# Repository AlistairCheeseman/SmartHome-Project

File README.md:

SmartHome-Project
=================

Final Year degree project to create a set of devices to create a smart home.

Hardware files are created in eagle with PDFs of finished pcbs labelled with which pcb layer they are. Hardware files are created from scratch and a custom library has been created for components not in the default eagle library.

Software has three sections.

	-	www
		copy this to the production web server. the files are based on php 5.6 HTML 5, using ajax and highcharts charting components (http://www.highcharts.com/ - free for non commercial uses).
		
	-	LFS
		This contains a set of manually written build scripts (toolchain and Filesystem) and pre-writted configuration files. After both files (install-*.sh) have been executed on a linux machine there will be a working Linux filesystem. Be sure to change configuration file (buildscript.sh) variables to suit your setup!

	-	Apps
		This contains source for all custom written applications on the server.

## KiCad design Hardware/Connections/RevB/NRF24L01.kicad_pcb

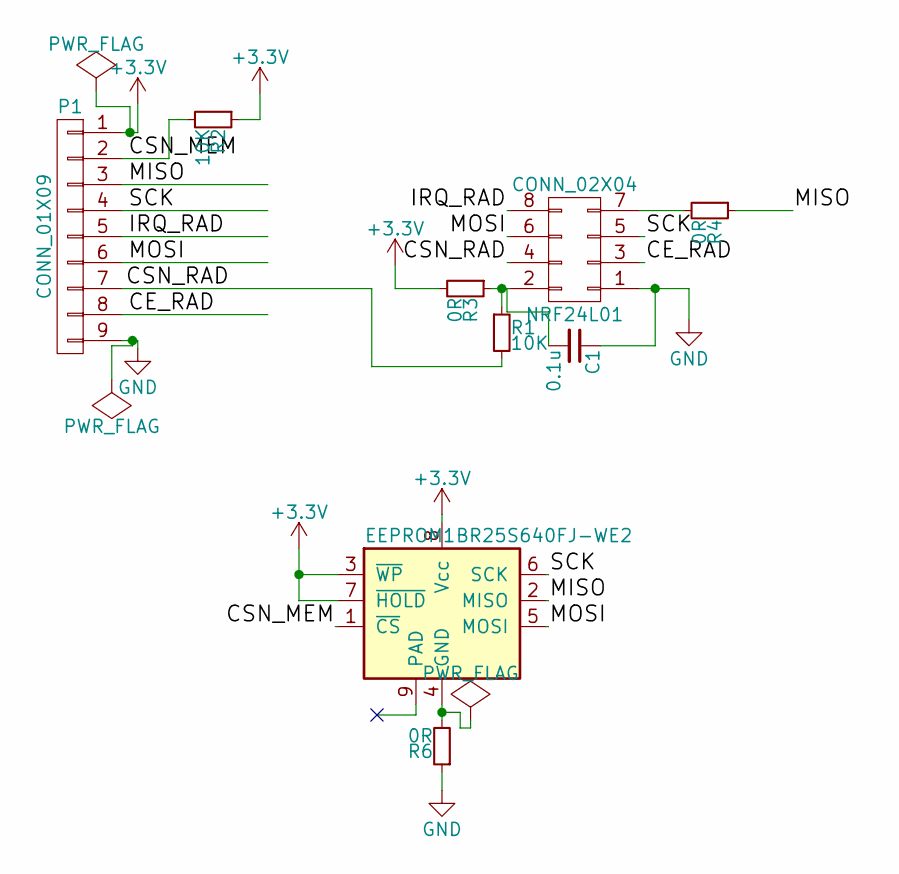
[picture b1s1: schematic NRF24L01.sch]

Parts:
C1: 0.1u; C_1206_HandSoldering
EEPROM1: BR25S640FJ-WE2; SOP8
NRF24L01: CONN_02X04; Pin_Header_Straight_2x04SMD
P1: CONN_01X09; Pin_Header_Straight_1x09
R1, R2: 10K; R_1206_HandSoldering
R3, R4, R6: 0R; R_1206_HandSoldering

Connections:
+3V3: EEPROM1.3 (~WP), EEPROM1.7 (~HOLD), EEPROM1.8 (Vcc), P1.1, R2.1, R3.2
/CE_RAD: NRF24L01.3, P1.8
/CSN_MEM: EEPROM1.1 (~CS), P1.2, R2.2
/CSN_RAD: NRF24L01.4, P1.7, R1.2
/IRQ_RAD: NRF24L01.8, P1.5
/MISO: EEPROM1.2 (MISO), P1.3, R4.1
/MOSI: EEPROM1.5 (MOSI), NRF24L01.6, P1.6
/SCK: EEPROM1.6 (SCK), NRF24L01.5, P1.4
GND: C1.1, NRF24L01.1, P1.9, R6.1
unnamed: C1.2, NRF24L01.2, R1.1, R3.1
unnamed: EEPROM1.4 (GND), R6.2
unnamed: NRF24L01.7, R4.2

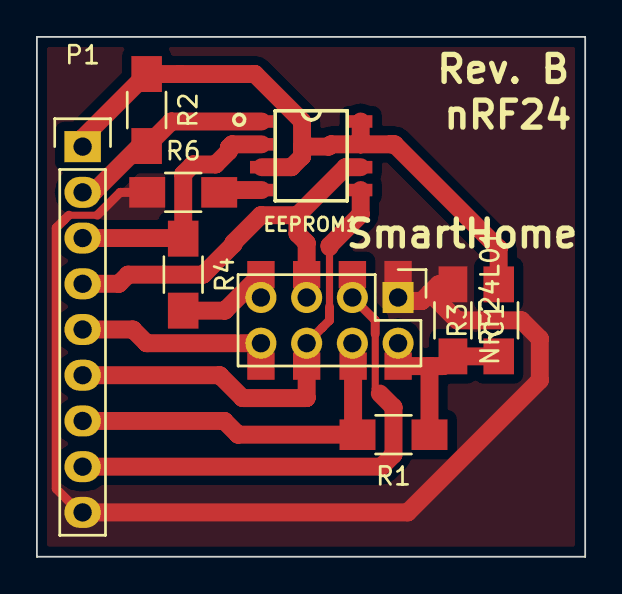
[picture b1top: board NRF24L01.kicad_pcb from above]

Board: 2 copper layers, 30.5 x 28.9 mm, 9 parts (0 on the bottom side), 12 nets.

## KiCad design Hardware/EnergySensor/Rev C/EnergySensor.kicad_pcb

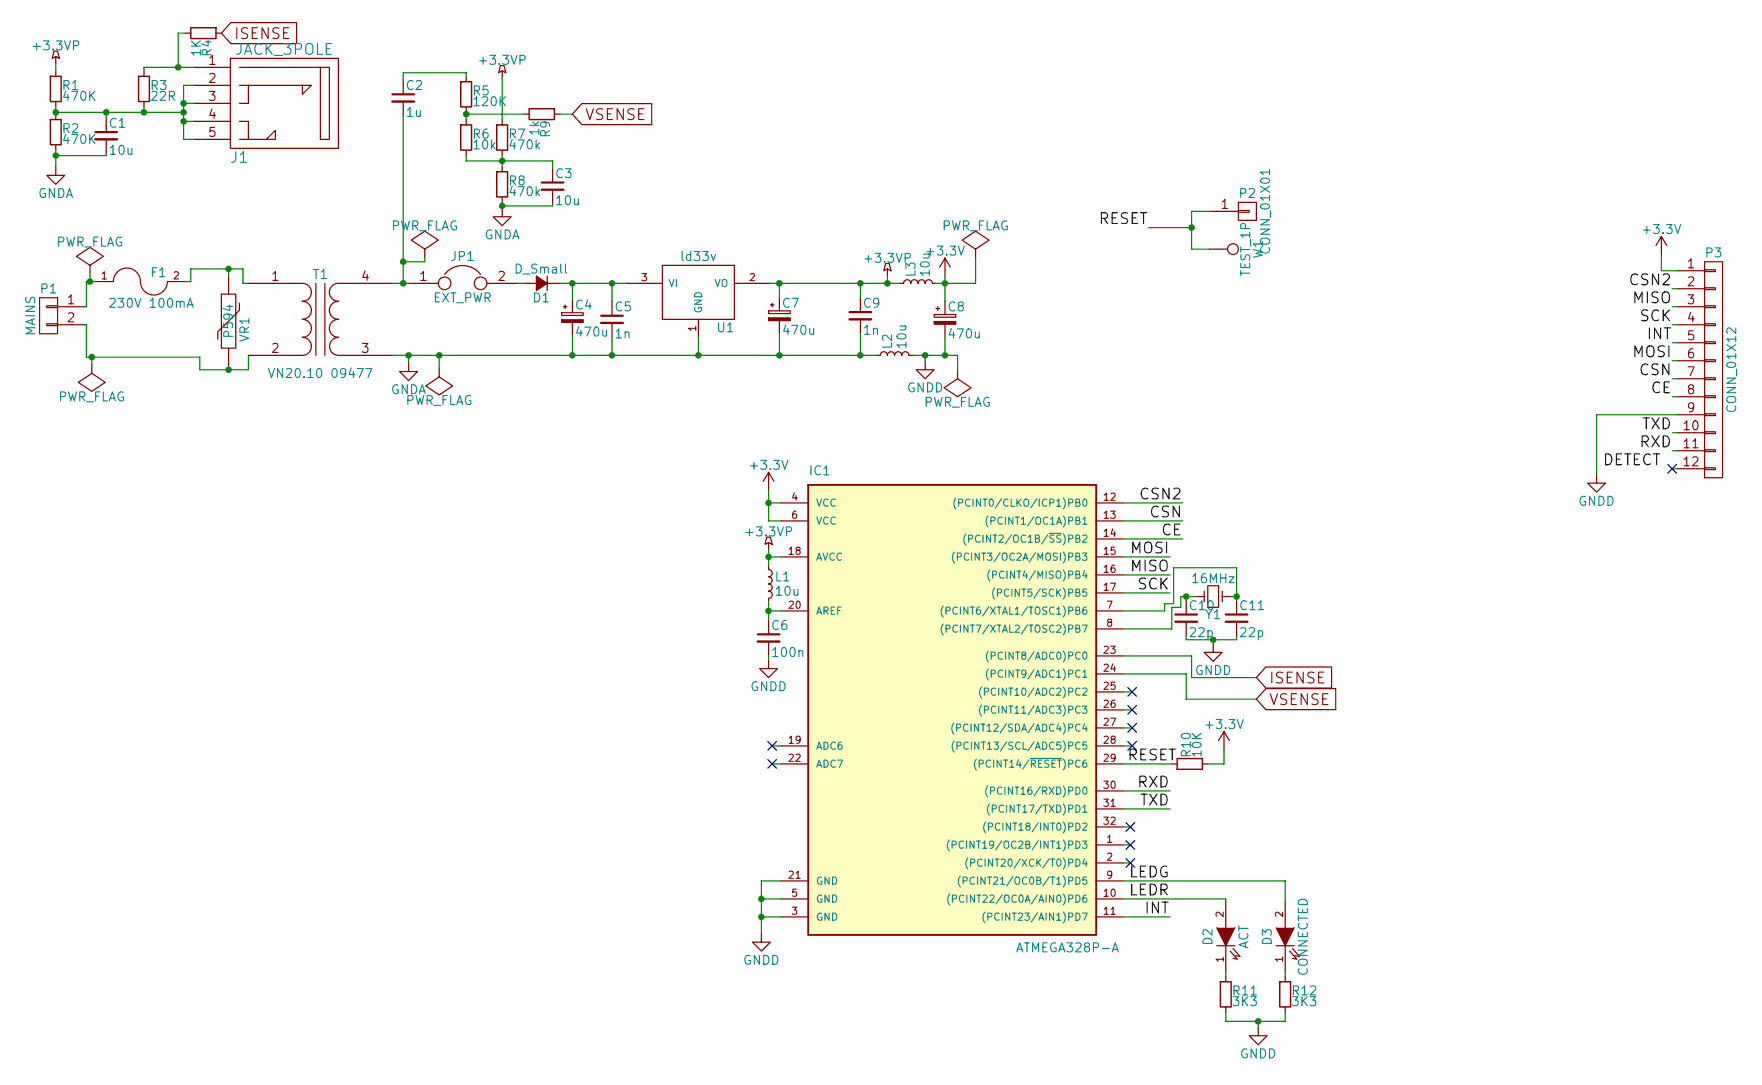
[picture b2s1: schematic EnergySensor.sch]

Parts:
C1, C3: 10u; C_1206_HandSoldering
C2: 1u; C_1206_HandSoldering
C4, C7, C8: 470u; c_elec_5x4.5
C5, C9: 1n; C_1206_HandSoldering
C6: 100n; C_1206_HandSoldering
C10, C11: 22p; C_1206_HandSoldering
D1: D_Small; MELF-RM10_Universal_Handsoldering
D2: ACT; LED-0805
D3: CONNECTED; LED-0805
F1: 230V 100mA; Fuse_SMD1206_HandSoldering
IC1: ATMEGA328P-A; TQFP-32_7x7mm_Pitch0.8mm
J1: JACK_3POLE
JP1: EXT_PWR; Socket_Strip_Straight_1x02
L1, L2, L3: 10u; Inductor_1212
P1: MAINS; AK300-2
P2: CONN_01X01; Pin_Header_Straight_1x01
P3: CONN_01X12; Socket_Strip_Angled_1x12
R1, R2: 470K; R_1206_HandSoldering
R3: 22R; R_1206_HandSoldering
R4: 1K; R_1206_HandSoldering
R5: 120K; R_1206_HandSoldering
R6: 10k; R_1206_HandSoldering
R7, R8: 470k; R_1206_HandSoldering
R9: 1k; R_1206_HandSoldering
R10: 10K; R_1206_HandSoldering
R11, R12: 3K3; R_1206_HandSoldering
T1: VN20.10 09477; TEZ-22x24
U1: ld33v; TO-220_Neutral123_Vertical
VR1: P594; RV_Disc_D7_W3.4_P5
W1: TEST_1P; Measurement_Point_Round-SMD-Pad_Big
Y1: 16MHz; Crystal_HC49-SD_SMD

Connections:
+3.3VP: C7.1, C9.1, IC1.18 (AVCC), L1.1, L3.1, R1.1, R7.1, U1.2 (VO)
+3V3: C8.1, IC1.4 (VCC), IC1.6 (VCC), L3.2, P3.1, R10.2
/CE: IC1.14 ((PCINT2/OC1B/~SS~)PB2), P3.8
/CSN: IC1.13 ((PCINT1/OC1A)PB1), P3.7
/CSN2: IC1.12 ((PCINT0/CLKO/ICP1)PB0), P3.2
/INT: IC1.11 ((PCINT23/AIN1)PD7), P3.5
/LEDG: D3.2 (A), IC1.9 ((PCINT21/OC0B/T1)PD5)
/LEDR: D2.2 (A), IC1.10 ((PCINT22/OC0A/AIN0)PD6)
/MISO: IC1.16 ((PCINT4/MISO)PB4), P3.3
/MOSI: IC1.15 ((PCINT3/OC2A/MOSI)PB3), P3.6
/RESET: IC1.29 ((PCINT14/~RESET~)PC6), P2.1, R10.1, W1.1
/RXD: IC1.30 ((PCINT16/RXD)PD0), P3.11
/SCK: IC1.17 ((PCINT5/SCK)PB5), P3.4
/TXD: IC1.31 ((PCINT17/TXD)PD1), P3.10
GNDA: C1.2, C3.2, C4.2, C5.2, C7.2, C9.2, L2.1, R2.2, R8.2, T1.3 (SA), U1.1 (GND)
GNDD: C6.2, C8.2, C10.2, C11.2, IC1.3 (GND), IC1.5 (GND), IC1.21 (GND), L2.2, P3.9, R11.2, R12.2
ISENSE: IC1.23 ((PCINT8/ADC0)PC0), R4.1
unnamed: C1.1, J1.2, J1.3, J1.4, J1.5, R1.2, R2.1, R3.2
unnamed: C2.1, R5.1
unnamed: C2.2, JP1.1, T1.4 (SB)
unnamed: C3.1, R6.2, R7.2, R8.1
unnamed: C4.1, C5.1, D1.1 (K), U1.3 (VI)
unnamed: C6.1, IC1.20 (AREF), L1.2
unnamed: C10.1, IC1.8 ((PCINT7/XTAL2/TOSC2)PB7), Y1.2
unnamed: C11.1, IC1.7 ((PCINT6/XTAL1/TOSC1)PB6), Y1.1
unnamed: D1.2 (A), JP1.2
unnamed: D2.1 (K), R11.1
unnamed: D3.1 (K), R12.1
unnamed: F1.1, P1.1
unnamed: F1.2, T1.1 (AA), VR1.1
unnamed: J1.1, R3.1, R4.2
unnamed: P1.2, T1.2 (AB), VR1.2
unnamed: R5.2, R6.1, R9.2
VSENSE: IC1.24 ((PCINT9/ADC1)PC1), R9.1

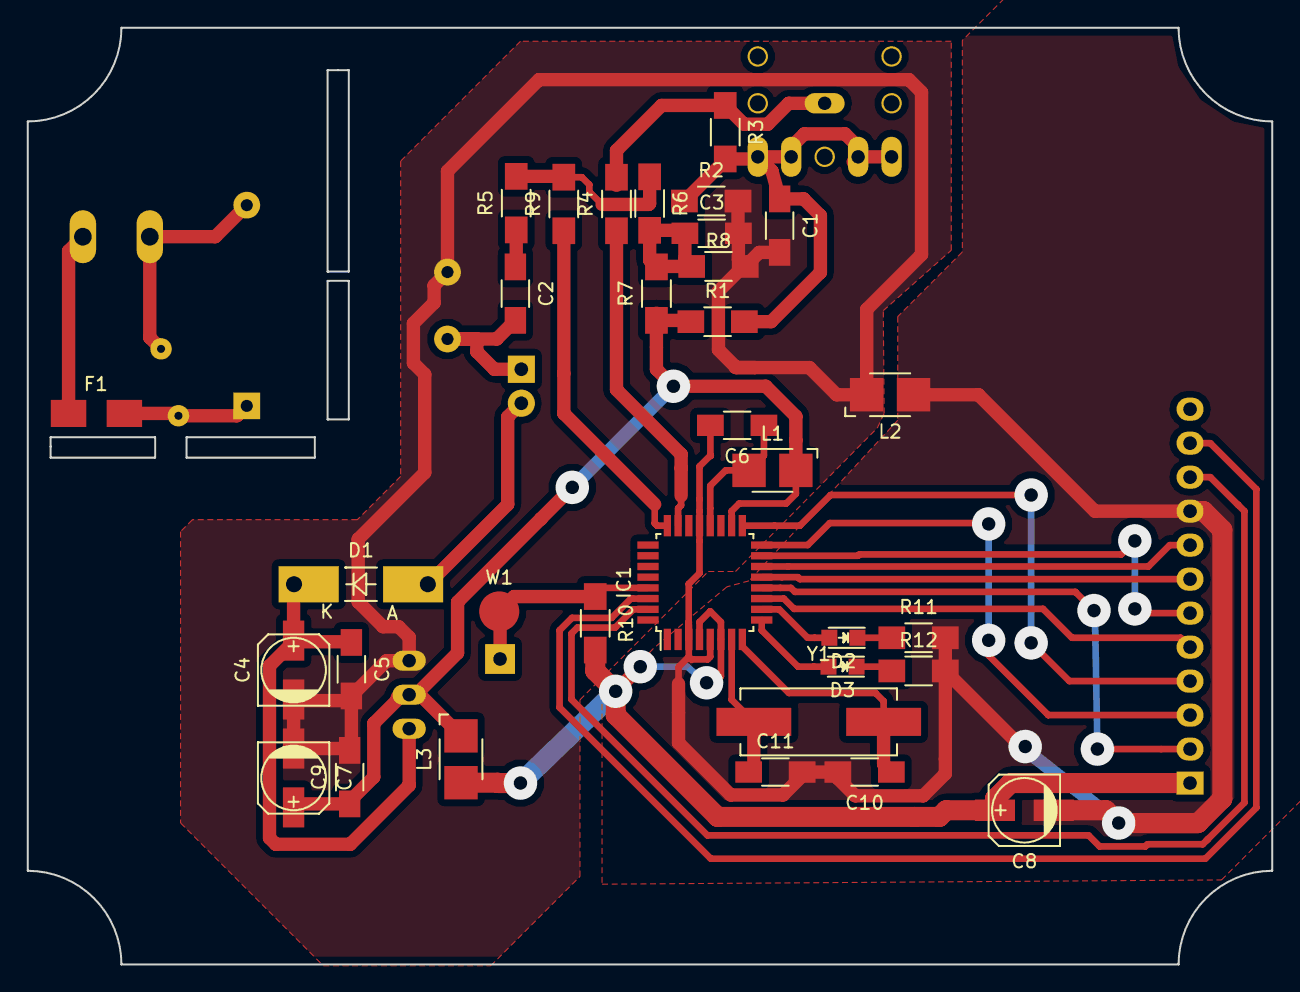
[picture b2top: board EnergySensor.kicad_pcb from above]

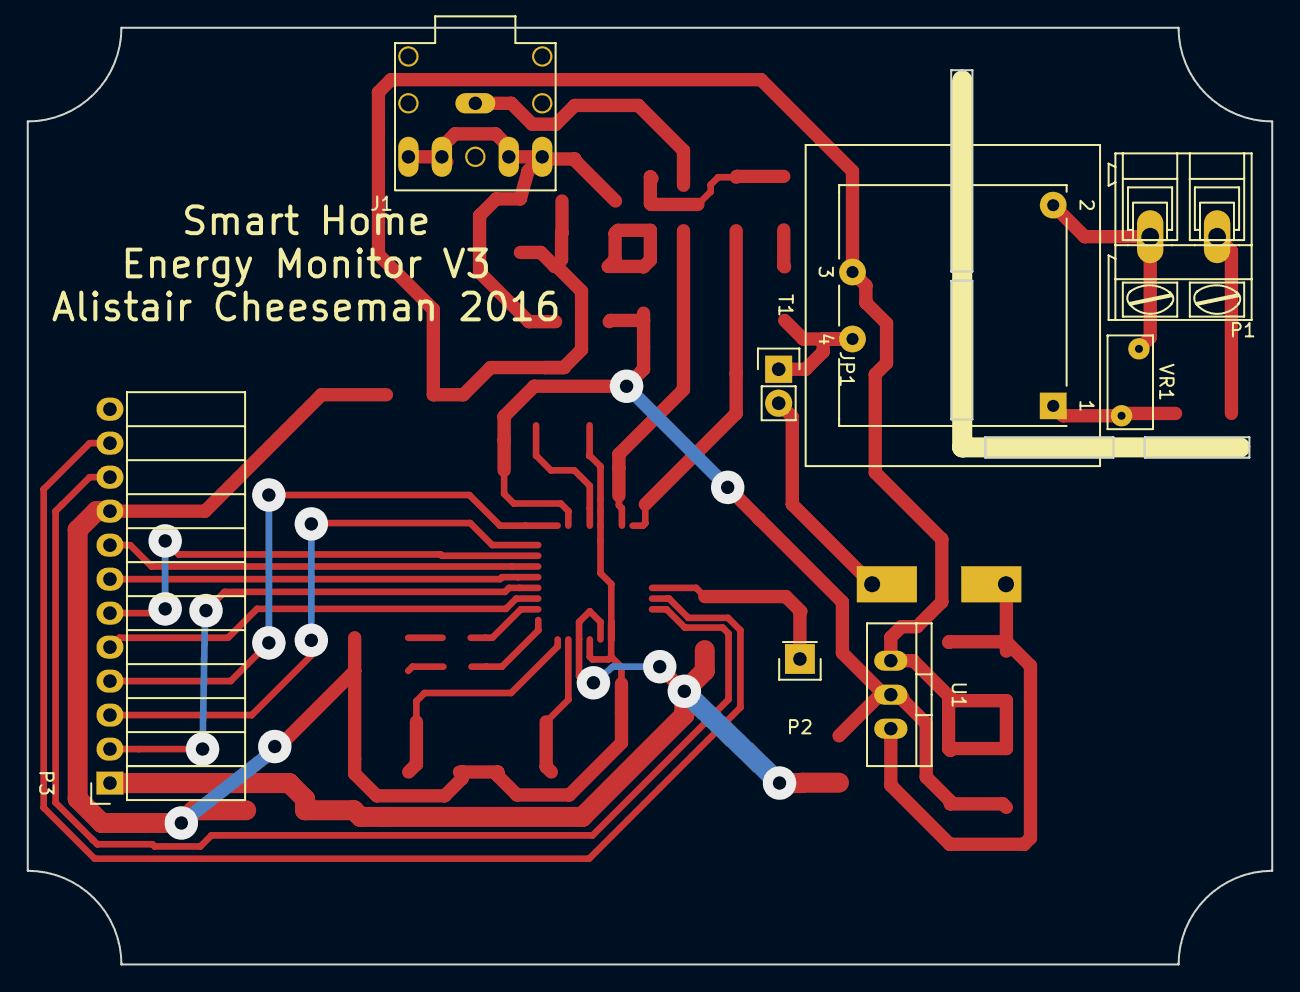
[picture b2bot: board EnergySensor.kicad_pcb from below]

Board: 2 copper layers, 93.0 x 70.0 mm, 41 parts (8 on the bottom side), 34 nets.

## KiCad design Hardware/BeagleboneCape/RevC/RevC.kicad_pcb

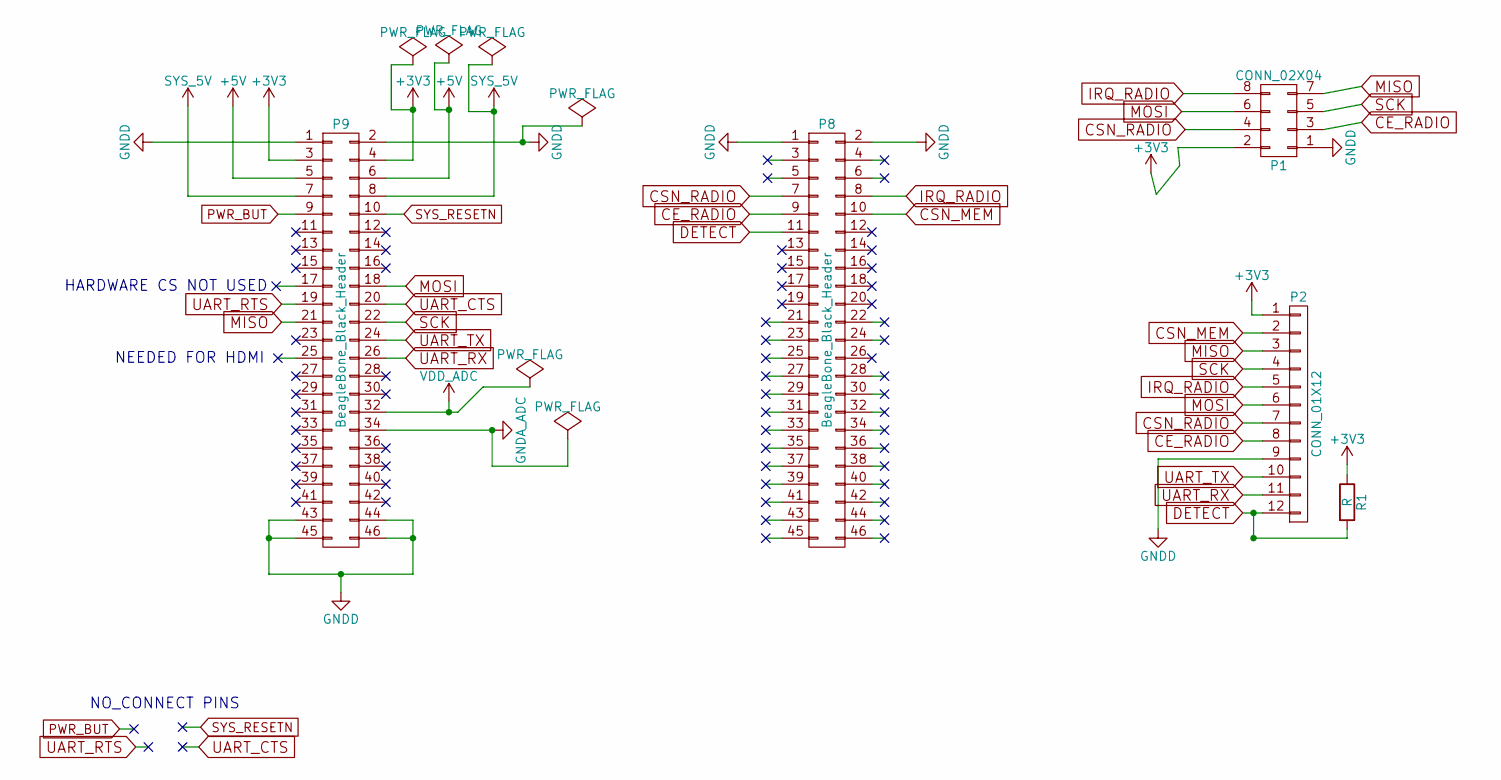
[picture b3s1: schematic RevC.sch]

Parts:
P1: CONN_02X04; Pin_Header_Straight_2x04
P2: CONN_01X12; Pin_Header_Straight_1x12
P8, P9: BeagleBone_Black_Header; Socket_BeagleBone_Black
R1: R; R_1210_HandSoldering

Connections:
+3V3: P1.2, P2.1, P9.3, P9.4, R1.1
+5V: P9.5, P9.6
CE_RADIO: P1.3, P2.8, P8.9
CSN_MEM: P2.2, P8.10
CSN_RADIO: P1.4, P2.7, P8.7
DETECT: P2.12, P8.11, R1.2
GNDA_ADC: P9.34
GNDD: P1.1, P2.9, P8.1, P8.2, P9.1, P9.2, P9.43, P9.44, P9.45, P9.46
IRQ_RADIO: P1.8, P2.5, P8.8
MISO: P1.7, P2.3, P9.21
MOSI: P1.6, P2.6, P9.18
PWR_BUT: P9.9
SCK: P1.5, P2.4, P9.22
SYS_5V: P9.7, P9.8
SYS_RESETN: P9.10
UART_CTS: P9.20
UART_RTS: P9.19
UART_RX: P2.11, P9.26
UART_TX: P2.10, P9.24
VDD_ADC: P9.32

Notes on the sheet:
NEEDED FOR HDMI
HARDWARE CS NOT USED
NO_CONNECT PINS

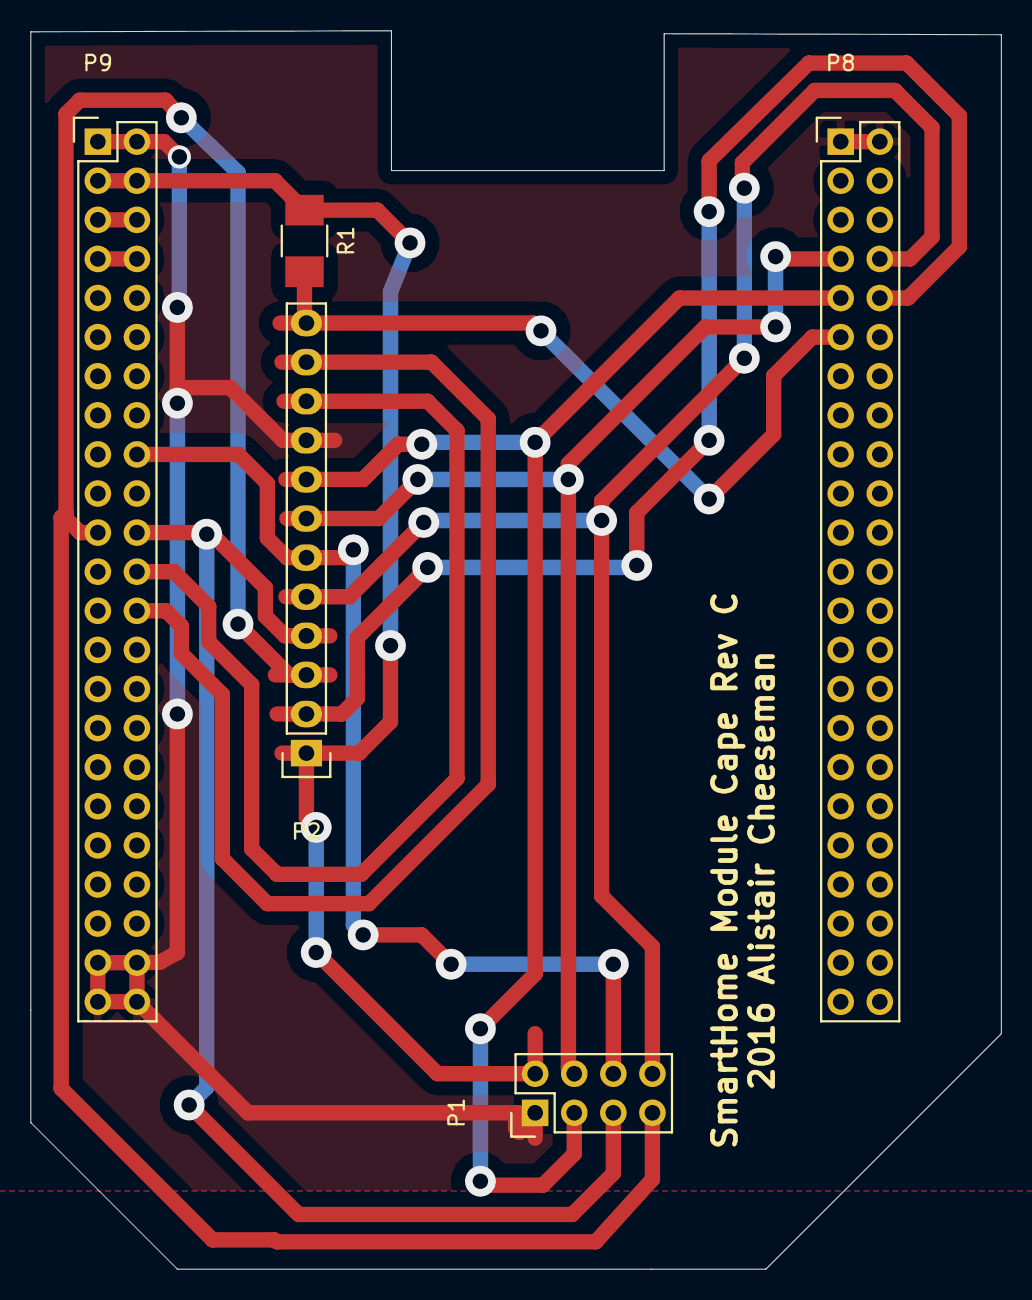
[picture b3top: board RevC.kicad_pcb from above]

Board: 2 copper layers, 63.1 x 80.5 mm, 5 parts (0 on the bottom side), 14 nets.

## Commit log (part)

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2014-12-04 Initial Commit of current PCBs
2014-12-08 Added Linux From Scratch (LFS) style build scripts and files. However the build scripts are found to be flawed.
2015-01-20 updated build scripts for a more automated procedure. Additionally applied new packages. However the build script is missing creation of a working SPI dtb. (see https://github.com/RobertCNelson/dtb-r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
2015-01-20 fixed mosquitto location on startup script. fixed script not setting executable on services fixed startupscript not setting LEDs to off
2015-01-25 removed files that were not meant to be added to git repo
2015-01-25 Updated PDF PCB files with Document outline mark. Fixed missing Name for NRF connector. Updated BOM to be correctly formatted.
2015-01-30 added php & apache packages. Still need to fix httpd being set with wrong directory location
2015-01-30 updated V2 ( Rev B) Board to use SMD only components where possible. Using 1206 Components
2015-02-01 Updated website to use SQLite. Sucessfully got graph pulling and rendering data from SQL
2015-02-01 added high power components for energy sensor. transformer needs to be sorted.
2015-02-01 created blank NRF program to work NRF wireless module ( added SPI and GPIO classes to handle hardware functions
2015-02-01 updated config to remove timezone error. Updated new value to prevent <1 values being refused.
2015-02-02 added simple start stop status restart however script still very lacking and due to be developed
2015-02-03 added marker to board file to allow for better silkscreen alignment
2015-02-06 added sqlite test program and sql classes
2015-02-06 added min value for power scale
2015-02-06 imporoved symbol
2015-02-06 initial mockup of heating controller
2015-02-06 created a programmer to allow for programming through the comms port
2015-02-12 updated to fix bug where spi would not fully work. due to other enabled devices.
2015-02-12 updated beaglebone cape and added pdf build files
2015-02-12 updated to fuse and varistor arrangements
2015-02-12 updated project files
2015-02-12 updated web layer to reflect logic layer changes
2015-02-12 added power outlet board
2015-02-12 updated git ignore files
2015-02-22 updated sql functions with new working sql schema
2015-02-22 updated styling for website and created base layer
2015-02-23 added basic components still awaiting Vreg and sensor devices
2015-02-23 Updated bug where script was in DOS format not NIX format
2015-02-23 fixed incorrect push. nfs and local files were mixed up
2015-02-23 fixed missing parenthesis
2015-02-24 Updated to make program take command line arguments correctly
2015-02-24 updated get_data to get a more diverse set of data
2015-02-27 updated wireless program to work as a simple two way UDP to Wireless bridge
2015-03-02 removed debug files and updated gitignore
2015-03-03 fixed bug where stated size and recieved size were mixed up
2015-03-03 added start up script for wireless bridge
2015-03-03 Updated to use new device notation for shorter topics
2015-03-03 updated output to allow for start-stop-daemon to be used.
2015-03-06 removed unneeded delays. added recieved message progcessing. fixed bug where packets would get lost. NOTE: this is due to network.tick being called by other functions when is should ONLY be called fr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
2015-03-09 added room listing populating by javascript (json ajax requests)
2015-03-10 Updated wrong fuse holder and processor footprint
2015-03-11 Updated issue where httpd would not find httpd headers
2015-03-11 updated to fix incorrect pin assignments
2015-03-11 updated to correct componnent values and minor tweaks
2015-03-11 updated moved to new revision as Rev A has already been produced. Added inductor to clean output power rail.
2015-03-11 updated BOM to match order
2015-03-12 updated web interface and added basic room & device functions
2015-03-13 added new library to correct incorrect footprint for LTV816S
2015-03-13 updated to list different categories of sensors (imporves readability)
2015-03-15 updated to prevent any caching of files
2015-03-15 added new library for 3.5mm jack
2015-03-16 updated component values
2015-03-16 updated gitignore to ignore AVR Firmware build files
2015-03-19 removed testing page to update variables
2015-03-20 Updated Rev B to reflect beneficial changes with Rev A pratical application, added noise suppressor to ARef. updated smoothing Ref Caps to match package. Added Additional Smoothing capacitors (due to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
2015-03-20 fixed dynamic power size message
2015-03-21 fixed typos on index page and added acknowledgements
2015-03-21 added a better printout (compressed more and HEX printing correctly (2 Digits per byte)
2015-03-21 added fix where packets would be massivley huge. Added increased client support to main()
2015-03-21 fixed incorrect resistor footprints. Added AGND Isolation Inductor. Added Silk Text. Moved Component Labels
2015-03-21 Renamed Lighting controller to lightswitch. Updated VTX supply text
2015-03-21 created mock up of Board
2015-03-22 initial mock up of lightswitch component placement
2015-03-22 updated etch and create TOP etch for print tests
2015-03-23 generated ETCH and RESIST Masks
2015-03-28 updated net css to use new styling from http://www.lavishbootstrap.com/. Added missing Sensor pages - (edit delete new). Added support to set a sensor request to have multiple destinations
2015-03-28 updated JSON PHP requests to match Web interface changes
2015-03-28 updated gitignore for future Apps
2015-03-28 fixed line spacing
2015-03-28 moved delay and increased to allow the delay to actually benefit the tick() function
2015-03-28 changed to get all message Ids on boot and publish to the ID rather than getting the Id then publishing, helped with response times. also sped up connects, as was missing connack packets due to delay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
2015-03-30 added simple packet routing ( hardcoded routing into program).
2015-03-31 added support for dynamic creation of addresses based on level and id.
2015-03-31 updated ignore to ignore .atsuo files
2015-03-31 fixed bug where if payload was bigger than 1 the packet would be chopped short.
2015-03-31 updated graph container name to match rest of website
2015-03-31 Fixed graph referencing. ( changed from container to sensorGraph) added suffix for power data for tooltip added processing of power compound data for set sensor types.
2015-03-31 created simple power measurement routine with calibrated sensors. still to add power angle support and real power calculations.
2015-03-31 changed the sensor history link to pass the control type aswell as the sensorid
2015-04-01 MASSIVE BUG - Listening on 000 and transmitting to it would cause messages to be sent all over the place. It turned out that the address is not an address of the device but and address of the COMMUNI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
2015-04-02 created initial schematic and basic component placements
2015-04-03 updated processoor to be surface mount. created intial route for pcb tracks. Had to use dual layer board to allow for small form factor
2015-04-03 fixed indentations, and changed wireless --> UDP wording to better show data direction changed to UDP <-- Wireless
2015-04-03 added little flash of lights at beginning and fixed indentation
2015-04-03 indented and added a timeout for waitResponse()
2015-04-03 moved datasheets into repository
2015-04-04 indented and swet graphs to use Area specific date times ( accounts for BST, GMT etc)
2015-04-04 now using the functions.js file to draw the power graph, modified the wording on the graph too
2015-04-04 added pdf of Etch layers.
2015-04-04 added 0 topicId checking to double check that the topicid is valid. topicid=0 if no response
2015-04-04 added code region to make common code hideable
2015-04-04 pragma region works in ide but breaks compile
2015-04-05 added heating controller header
2015-04-05 added simple heating controller code. ( note close copy of power outlet code)
2015-04-06 added board information text
2015-04-06 updated silk to Include hole patterns
2015-04-06 updated pdf to reflect postscript changes
2015-04-06 updated board text to be the correct way round
2015-04-07 included the calculations for the conversion from the values recieved from the sensor. ( referenced from datasheet) and changed read order.
2015-04-07 corrected filtering to work by control type category ( output, sensor, request)
2015-04-07 added temperature humidity and LUX to sensor History
2015-04-08 modified chart type of temperature sensor to give a smoother line.
2015-04-08 modified table to be accessible by javascript and removed sample data, and added javascript function to populate table
2015-04-08 added environment data view
2015-04-08 removed unnecessary udp connection and configured the additional client (5)
2015-04-09 moved javascript to show correct form for sensor data to sepearte function to enable the ability to call it manually which fixes bug where on ititial load the new sensor form would not show correct d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
2015-04-09 changed where onchange is called first time to update the default selection of the page. In old position it would cause the mapping list to be duplicated
2015-04-09 added delays between publish to allow server to process requests
2015-04-09 created basic working code
2015-04-09 added filter to only check for rules that can be processed by the scheduler
2015-04-09 updated Scheduler to put lastexec time into rule dbif rule is ran. also corrected filtering of what rules to process
2015-04-09 updated scheduler to delete temporary rules once they have been executed
2015-04-09 added delete page for rules
2015-04-09 fixed case for variables
2015-04-10 added sqlopen threaded access. added retry loop to log function. added more information to sql errors. Indented page correctly. merged some sql statements.
2015-04-16 added SQL commands to get sensorId and to get rule information
2015-04-16 fixed issue where RuleTypeId would not be loaded.
2015-05-07 updated BOM with finalised pricelist
2015-10-04 added version check script from CLFS website
2015-10-05 created buildscript that uses KMX mirror for sources
2015-10-05 updated rest of links to kmx server
2015-10-07 added check for lzop
2015-10-07 commit of some old changes that were missed from final commit
2015-10-17 added startup script for logiclayer to resources
2015-10-19 Added BC to version check
2016-01-09 started creation of RevC Beaglebone cape. - aims to add EEPROM programming capability and full support of any comms module
2016-01-09 added beaglebone black reference manual
2016-01-10 added fix to force 3.14 kernel build. also updated mirror location
2016-01-11 moved gitignore
2016-01-12 initial mockup of board layout, removed 8 pin connector in favour of the single-module board
2016-01-19 fixed hang on no arguments
2016-05-22 Update install-toolchain.sh
    added reminder to upgrade openssl version
2016-05-29 updated to new versions of files - totest
2016-07-03 Updated database generation script and added default values. updated the databaseexists to use an active table rather than a defunct table
2016-07-03 added netbeans files to gitignore
2016-07-03 updated board layout and exported svg files
2016-07-03 initial mockup of energysensor RevC
2016-07-10 moved energy sensor to nice case and various tweaks
2016-07-10 moved text and created exports for energy sensor
2016-08-05 fixed missing wire
2016-08-08 added lsdiff to version check
2016-08-09 added simple NFS/LOCAL switch and internal filestore mirror/direct option
2016-08-19 updated nameserver to be more generic
2016-08-19 created class to make logging simpler
2016-08-20 added global logging class to logiclayer made makefiles automatically source buildscript variables
2016-08-20 fixed missing makefile modifications to commit 02be7602c5a710074adab73ad601109a55723536
2016-08-20 added additonal files to gitignore
2016-11-01 Added support for GCC6 on the host to build and support for building mysql
2016-11-13 added missing finalise statement to SQL::GetRules
2016-11-14 changed to source relative buildscript rather than absolute buildscript
2016-11-18 moved all possible options to a common config file - to make changes easier to manage
2016-11-19 added large buffer for target topic payloads
2016-11-20 fixed bug trying to free already freed memory and added timeout to SQL connection to allow more reliable operation
2016-11-24 fixed TCF build and fixed up package commands
2016-11-24 fixed up makefiles to work on both native or cross builds
